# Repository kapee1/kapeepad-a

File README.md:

# kapeepad-a
Macropad with Seeeduino Xiao BLE and EC-11 encoder

**UNTESTED!!!**

* MX Switches
* 2u keys supported
* Battery - LiPo 301230

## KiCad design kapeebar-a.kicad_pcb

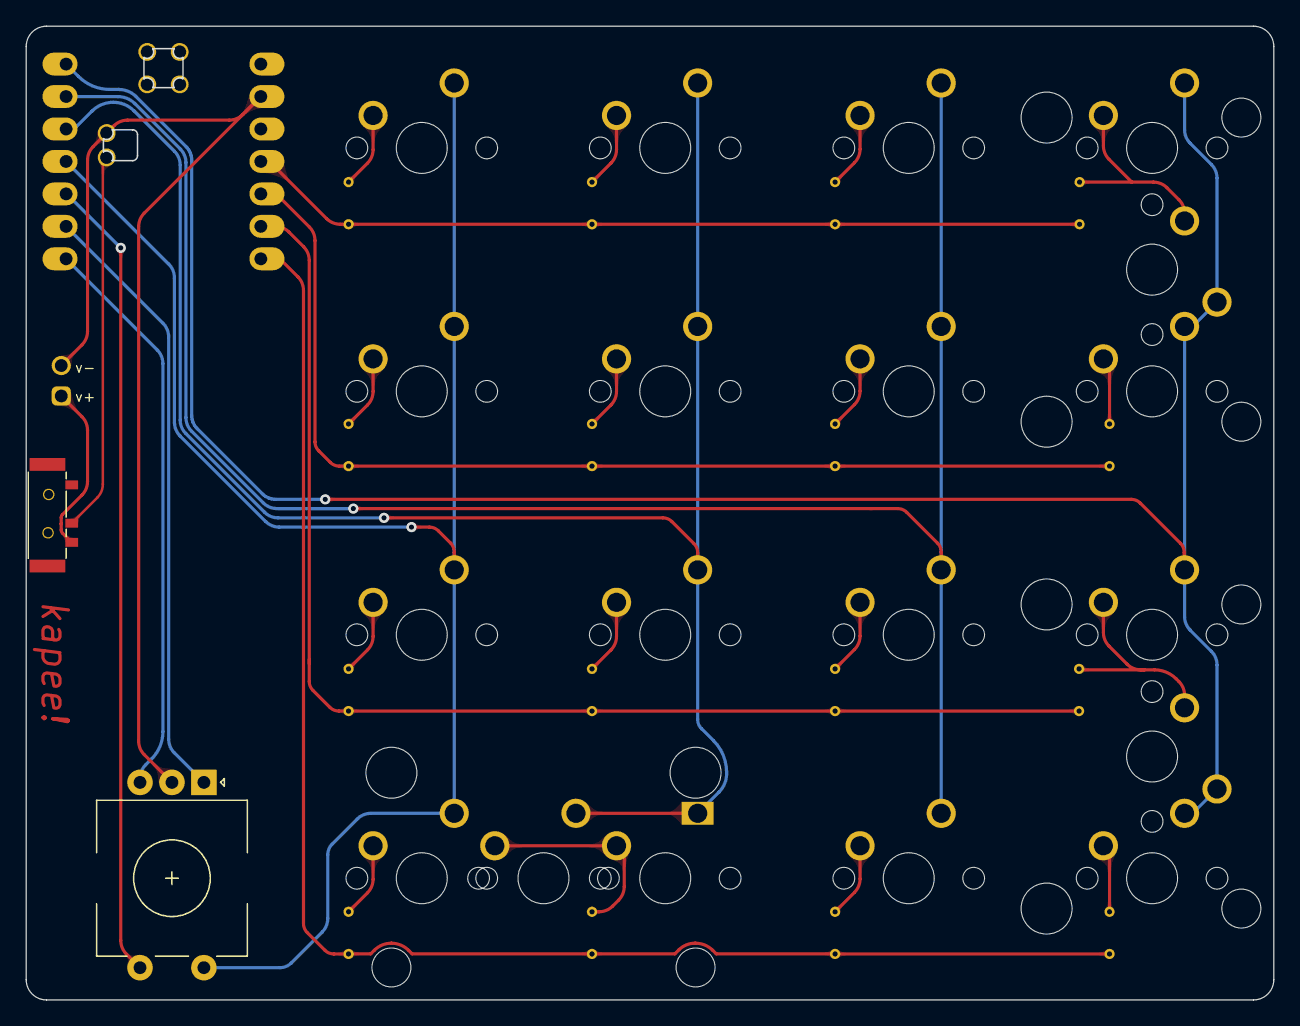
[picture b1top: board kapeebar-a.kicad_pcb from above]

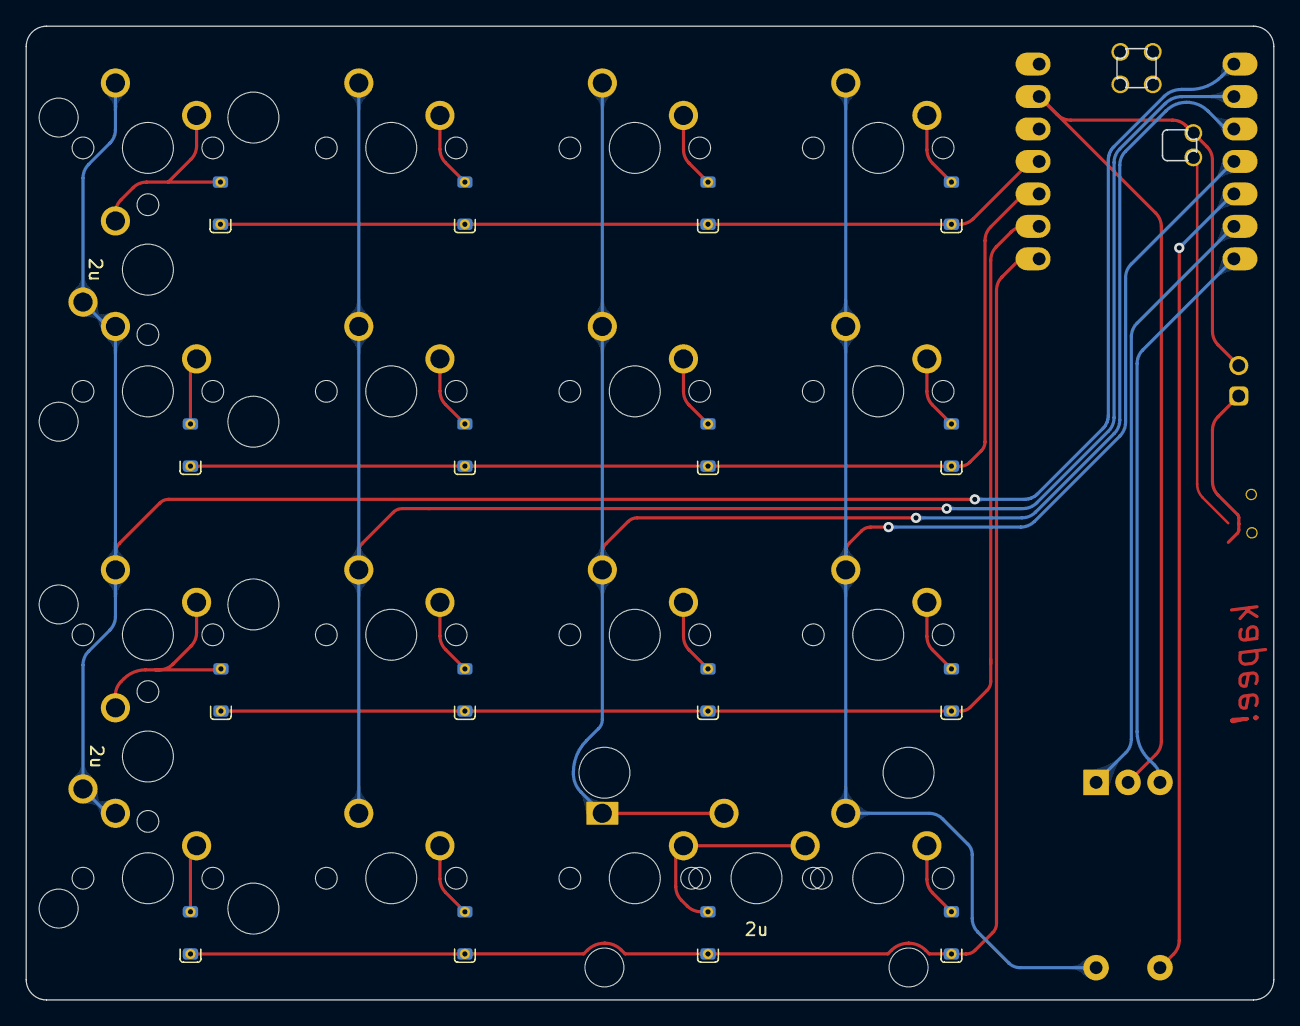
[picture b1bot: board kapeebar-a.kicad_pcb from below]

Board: 2 copper layers, 97.6 x 76.2 mm, 43 parts (16 on the bottom side), 30 nets.

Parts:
2u: MX; SW_MX
D1, D2, D3, D4, D5, D6, D7, D8, D9, D10, D11, D12, D13, D14, D15, D16: 1N4148W; D_SOD-123
J1: v+; BatteryPadSquare
J2: v-; BatteryPad
ST1, ST2, ST3: Stabilizer_MX_2u
SW1, SW2, SW3, SW4, SW5, SW6, SW7, SW8, SW9, SW10, SW11, SW13, SW14, SW17, SW18: MX; SW_MX
SW12, SW19: 2u; SW_MX
SW15: RotaryEncoder_Switch; RotaryEncoder_EC11
SW16: MX; SW_MX_one_square
U1: SeeeduinoXIAO; xiao-ble-smd-cutout
switch: MSK12C02

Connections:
ENC0: SW15.A, U1.6 (A5)
ENC1: SW15.B, U1.7 (A6)
GND: J2.1, SW15.C, U1.13 (GND), U1.20
unnamed: D4.2 (A), SW1.2
unnamed: D3.2 (A), SW2.2
unnamed: D2.2 (A), SW3.2
unnamed: D1.2 (A), SW4.2, SW12.2
unnamed: D8.2 (A), SW5.2
unnamed: D7.2 (A), SW8.2
unnamed: D6.2 (A), SW9.2
unnamed: D5.2 (A), SW13.2
unnamed: D12.2 (A), SW6.2
unnamed: D11.2 (A), SW7.2
unnamed: D10.2 (A), SW10.2
unnamed: D9.2 (A), SW11.2, SW19.2
unnamed: D16.2 (A), SW14.2
unnamed: 2u.2, D15.2 (A), SW16.2
unnamed: D14.2 (A), SW17.2
unnamed: D13.2 (A), SW18.2
V+: U1.19, switch.2
col0: SW1.1, SW5.1, SW6.1, SW14.1, SW15.S2, U1.4 (A3)
col1: 2u.1, SW2.1, SW7.1, SW8.1, SW16.1, U1.3 (A2)
col2: SW3.1, SW9.1, SW10.1, SW17.1, U1.2 (A1)
col3: SW4.1, SW11.1, SW12.1, SW13.1, SW18.1, SW19.1, U1.1 (A0)
row0: D1.1 (K), D2.1 (K), D3.1 (K), D4.1 (K), U1.11 (A10)
row1: D5.1 (K), D6.1 (K), D7.1 (K), D8.1 (K), U1.10 (A9)
row2: D9.1 (K), D10.1 (K), D11.1 (K), D12.1 (K), U1.9 (A8)
row3: D13.1 (K), D14.1 (K), D15.1 (K), D16.1 (K), U1.8 (A7)
row4: SW15.S1, U1.5 (A4)
vbat: J1.1, switch.3

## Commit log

2023-06-29 about project
